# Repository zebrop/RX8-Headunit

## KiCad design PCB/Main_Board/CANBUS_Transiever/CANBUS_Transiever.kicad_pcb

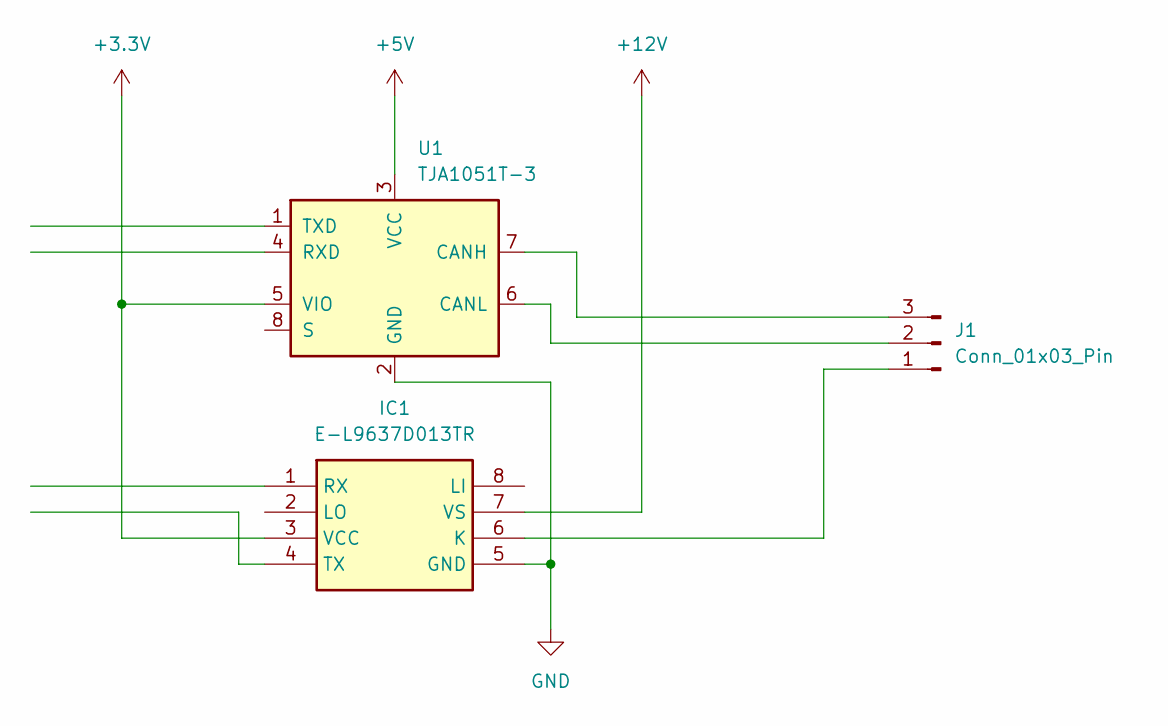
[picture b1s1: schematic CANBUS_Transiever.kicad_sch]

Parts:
IC1: E-L9637D013TR; SOIC127P600X175-8N; Mouser Part Number 511-E-L9637D013TR
J1: Conn_01x03_Pin; JST_PH_B3B-PH-K_1x03_P2.00mm_Vertical
U1: TJA1051T-3; SOIC-8_3.9x4.9mm_P1.27mm

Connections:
+3.3V: IC1.3 (VCC), U1.5 (VIO)
+5V: U1.3 (VCC)
+12V: IC1.7 (VS)
GND: IC1.5 (GND), U1.2 (GND)
unnamed: IC1.6 (K), J1.1
unnamed: J1.2, U1.6 (CANL)
unnamed: J1.3, U1.7 (CANH)

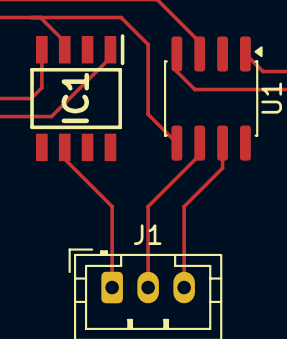
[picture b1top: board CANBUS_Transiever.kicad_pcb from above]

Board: 2 copper layers, 3 parts (0 on the bottom side), 5 nets.

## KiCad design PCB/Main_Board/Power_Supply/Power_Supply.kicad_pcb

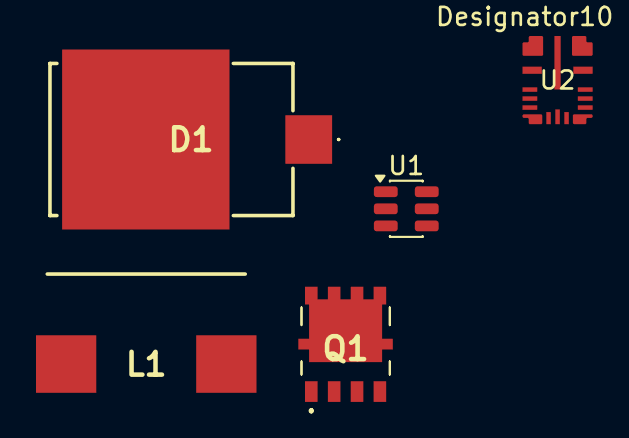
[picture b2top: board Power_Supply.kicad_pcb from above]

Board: 2 copper layers, 5 parts (0 on the bottom side), 4 nets, no tracks yet.

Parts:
D1: SM8S24A; SM8S24AHE3TP
L1: SRP1038AA-100M; INDPM110100X400N
Q1: NVMJS2D5N06CLTWG
U1: LM74700; SOT-23-6
U2: LM61480Q5RPHRQ1; RPH0016A

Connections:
+12V: Q1.1 (S_1), Q1.2 (S_2), Q1.3 (S_3), U1.6 (ANODE)
GND: D1.2 (A), U1.2 (GND)
unnamed: D1.1 (K), L1.1, Q1.5 (D_1), Q1.6 (D_2), Q1.7 (D_3), Q1.8 (D_4), Q1.10 (D_5), Q1.12 (D_6), Q1.13 (D_7), Q1.14 (D_8), U1.4 (CATHODE)
unnamed: Q1.4 (G), U1.5 (GATE)

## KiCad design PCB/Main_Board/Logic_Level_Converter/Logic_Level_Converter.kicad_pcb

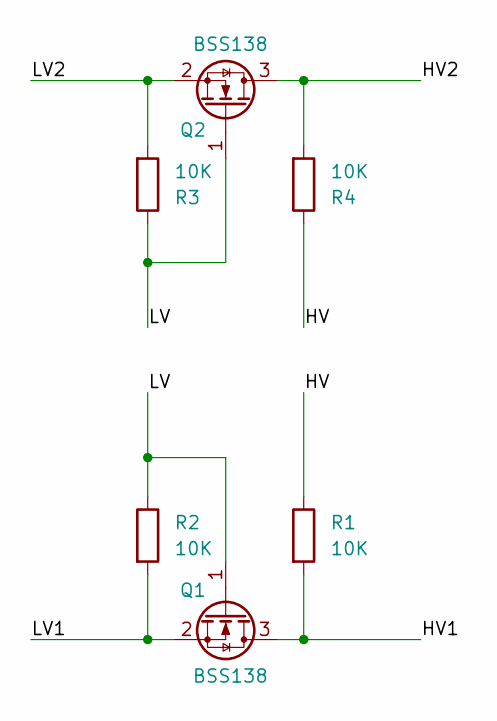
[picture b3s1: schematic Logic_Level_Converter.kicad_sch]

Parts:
Q1, Q2: BSS138; SOT-23
R1, R2, R3, R4: 10K; R_0603_1608Metric

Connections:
/HV: R1.1, R4.1
/HV1: Q1.3 (D), R1.2
/HV2: Q2.3 (D), R4.2
/LV: Q1.1 (G), Q2.1 (G), R2.1, R3.1
/LV1: Q1.2 (S), R2.2
/LV2: Q2.2 (S), R3.2

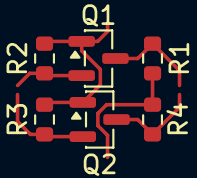
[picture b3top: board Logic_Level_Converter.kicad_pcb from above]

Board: 2 copper layers, 6 parts (0 on the bottom side), 6 nets.

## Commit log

2026-04-25 fix crash on startup
2026-04-25 Restructure CarPlay config and reduce render GPU pressure
2026-04-25 Linked phone connection status backend
2026-04-26 newbuttons/and ac wallpaper
2026-04-26 Completed UI for AC Page
2026-04-26 Mostly completed UI for MediaControls page
2026-04-27 Linked preset functionallity to the the EQ and kep persistent presets across app launches
2026-04-27 tidying up media page
2026-04-27 complete restructure
2026-04-27 removed redundant folder
2026-04-29 Started linking theme page together
2026-04-29 performance page front end skeleton completed
2026-05-03 3d model car on home page
2026-05-03 Clean QML modules and add Teensy telemetry integration
2026-05-06 added initial PCB Design Files
